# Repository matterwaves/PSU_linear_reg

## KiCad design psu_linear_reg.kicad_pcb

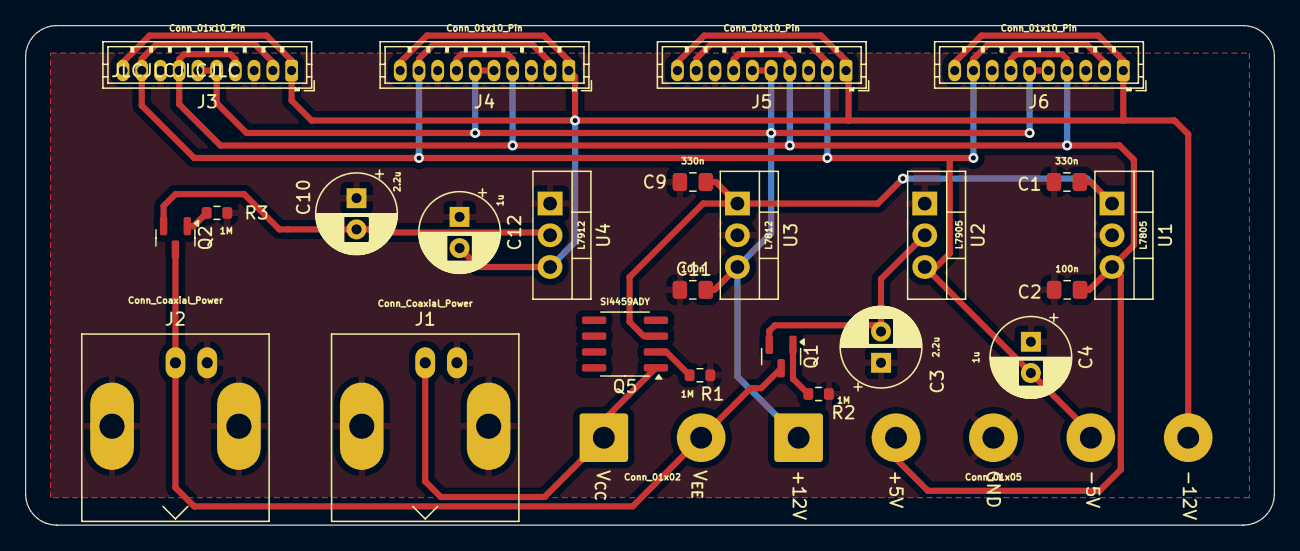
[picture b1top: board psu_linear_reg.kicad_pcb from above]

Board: 2 copper layers, 100.0 x 40.0 mm, 26 parts (0 on the bottom side), 13 nets.

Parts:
C1, C9: 330n; C_0805_2012Metric_Pad1.18x1.45mm_HandSolder
C2, C11: 100n; C_0805_2012Metric_Pad1.18x1.45mm_HandSolder
C3, C10: 2.2u; CP_Radial_D6.3mm_P2.50mm
C4, C12: 1u; CP_Radial_D6.3mm_P2.50mm
J1, J2: Conn_Coaxial_Power; BNC_Molex_0731385033
J3, J4, J5, J6: Conn_01x10_Pin; JST_ZH_B10B-ZR_1x10_P1.50mm_Vertical
J7: Conn_01x05; SolderWire-1sqmm_1x05_P7.8mm_D1.4mm_OD3.9mm
J8: Conn_01x02; SolderWire-1sqmm_1x02_P7.8mm_D1.4mm_OD3.9mm
Q1, Q2: AO3400A; SOT-23
Q5: SI4459ADY; SOIC-8_3.9x4.9mm_P1.27mm
R1, R2, R3: 1M; R_0603_1608Metric
U1: L7805; TO-220-3_Vertical
U2: L7905; TO-220-3_Vertical
U3: L7812; TO-220-3_Vertical
U4: L7912; TO-220-3_Vertical

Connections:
+5V: C2.1, J3.4, J3.7, J4.4, J4.7, J5.4, J5.7, J6.4, J6.7, J7.2, U1.3 (OUT)
+12V: C11.1, J3.5, J3.6, J4.5, J4.6, J5.5, J5.6, J6.5, J6.6, J7.1, U3.3 (OUT)
-5V: C4.2, J3.2, J3.9, J4.2, J4.9, J5.2, J5.9, J6.2, J6.9, J7.4, U2.3 (VO)
-12V: C12.2, J3.1, J3.10, J4.1, J4.10, J5.1, J5.10, J6.1, J6.10, J7.5, U4.3 (VO)
GND: C1.2, C2.2, C3.1, C4.1, C9.2, C10.1, C11.2, C12.1, J1.2 (Ext), J2.2 (Ext), J3.3, J3.8, J4.3, J4.8, J5.3, J5.8, J6.3, J6.8, J7.3, R1.2, R2.2, R3.2, U1.2 (GND), U2.1 (GND), U3.2 (GND), U4.1 (GND)
unnamed: Q1.1 (G), R2.1
unnamed: C3.2, Q1.2 (S), U2.2 (VI)
unnamed: Q2.1 (G), R3.1
unnamed: C10.2, Q2.2 (S), U4.2 (VI)
unnamed: Q5.2 (G), R1.1
unnamed: C1.1, C9.1, Q5.3 (S), U1.1 (IN), U3.1 (IN)
VCC: J1.1 (In), J8.1, Q5.1 (D)
VEE: J2.1 (In), J8.2, Q1.3 (D), Q2.3 (D)

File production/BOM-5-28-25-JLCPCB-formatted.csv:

Designator,Comment,Footprint,LCSC Part Number
"C1,C9",330n,Capacitor_SMD:C_0805_2012Metric_Pad1.18x1.45mm_HandSolder,C1740
"C2,C11",100n,Capacitor_SMD:C_0805_2012Metric_Pad1.18x1.45mm_HandSolder,C49678
"C3,C10",2.2u,Capacitor_THT:CP_Radial_D6.3mm_P2.50mm,
"C4,C12",1u,Capacitor_THT:CP_Radial_D6.3mm_P2.50mm,
"J1,J2",Conn_Coaxial_Power,matterwaves:BNC_Molex_0731385033,
"J3,J4,J5,J6",Conn_01x10_Pin,Connector_JST:JST_ZH_B10B-ZR_1x10_P1.50mm_Vertical,
"Q1,Q2",AO3400A,Package_SO:SOP-8_3.76x4.96mm_P1.27mm,C20917
Q5,SI4459ADY,Package_TO_SOT_SMD:SOT-23,C347475
"R1,R2,R3",1M,Resistor_SMD:R_0603_1608Metric,C2933267
U1,L7805,Package_TO_SOT_THT:TO-220-3_Vertical,
U2,L7905,Package_TO_SOT_THT:TO-220-3_Vertical,
U3,L7812,Package_TO_SOT_THT:TO-220-3_Vertical,
U4,L7912,Package_TO_SOT_THT:TO-220-3_Vertical,

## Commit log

2025-01-10 Added reverse polarity protection
2025-01-14 Added reverse polarity protection. PCB ready for ordering
2025-01-14 Added .drl file correctly. PCB ready for ordering
2025-05-19 rev 1.2. Fixed negative supply nmos protection
2025-05-29 Fixed -V polarity protection.
2025-05-29 V1.3 5-28-25 with -V polarity protection
2025-08-14 updated .zip files
